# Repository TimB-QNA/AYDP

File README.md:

AYDP
====

The Autonomous Yacht Development Platform project. A project to develop a fully autonomous sailing yacht which can safely navigate between pre-defined waypoints.

Setting up AYDP:

You will need:
  A model yacht
  A Raspberry PI and SDCard
  A USB wifi dongle (which works in access point mode) - or a PI3
  An MPU-9150 IMU board
  An AYDP Interface board (see the hardware directory)
  And a variety of wires, power supplies etc. to put them all together.

First install a copy of Raspbian to the PI by downloading the latest image from http://www.raspberrypi.org/downloads there are loads of examples of how to burn the image to an SD Card, but you'll end up with a command something like:

dd bs=32K if=2014-01-07-wheezy-raspbian.img  of=/dev/sdb

Next, boot and log into the pi, then expand the partitions on the SD Card and enable the SSH server at bootup. Ensure that your PI has internet connection over a wired network link and install your wifi dongle (wired internet helps when you need to download packages). With the PI still connected to the internet, turn it into a wifi access point by following the instructions at http://elinux.org/RPI-Wireless-Hotspot except that there is no need to set up IPTables for NAT (unless you want to augment AYDP with network devices, in which case, you're probably smart enough to work out that you'll probably need NAT for any sensible debugging). The next major installation is I2C. This is disabled by default, but can by enabled by following the tutorial at https://learn.adafruit.com/adafruits-raspberry-pi-lesson-4-gpio-setup/configuring-i2c except for the bits about python (because this project is written in C++).

To get the i2c functionality to work, comment any lines in /etc/modprobe.d/raspi-blacklist.conf. and ensure the following modules are in /etc/modules:

snd-bcm2835
i2c-bcm2708
i2c-dev

At present, however, you'll only be able to run the code as root. Given that this is an utterly hideous idea (for a number of security reasons), we need to enable user access to the parts we need for the code to run. To avoid this, you need to add your user to the i2c group thus:

useradd -g i2c pi

Install sshfs for development work...
apt-get install sshfs
add "pi" user to the fuse group.

For development work you will need to install the following packages:

apt-get install qt4-dev-tools
apt-get install libusb-1.0-0-dev

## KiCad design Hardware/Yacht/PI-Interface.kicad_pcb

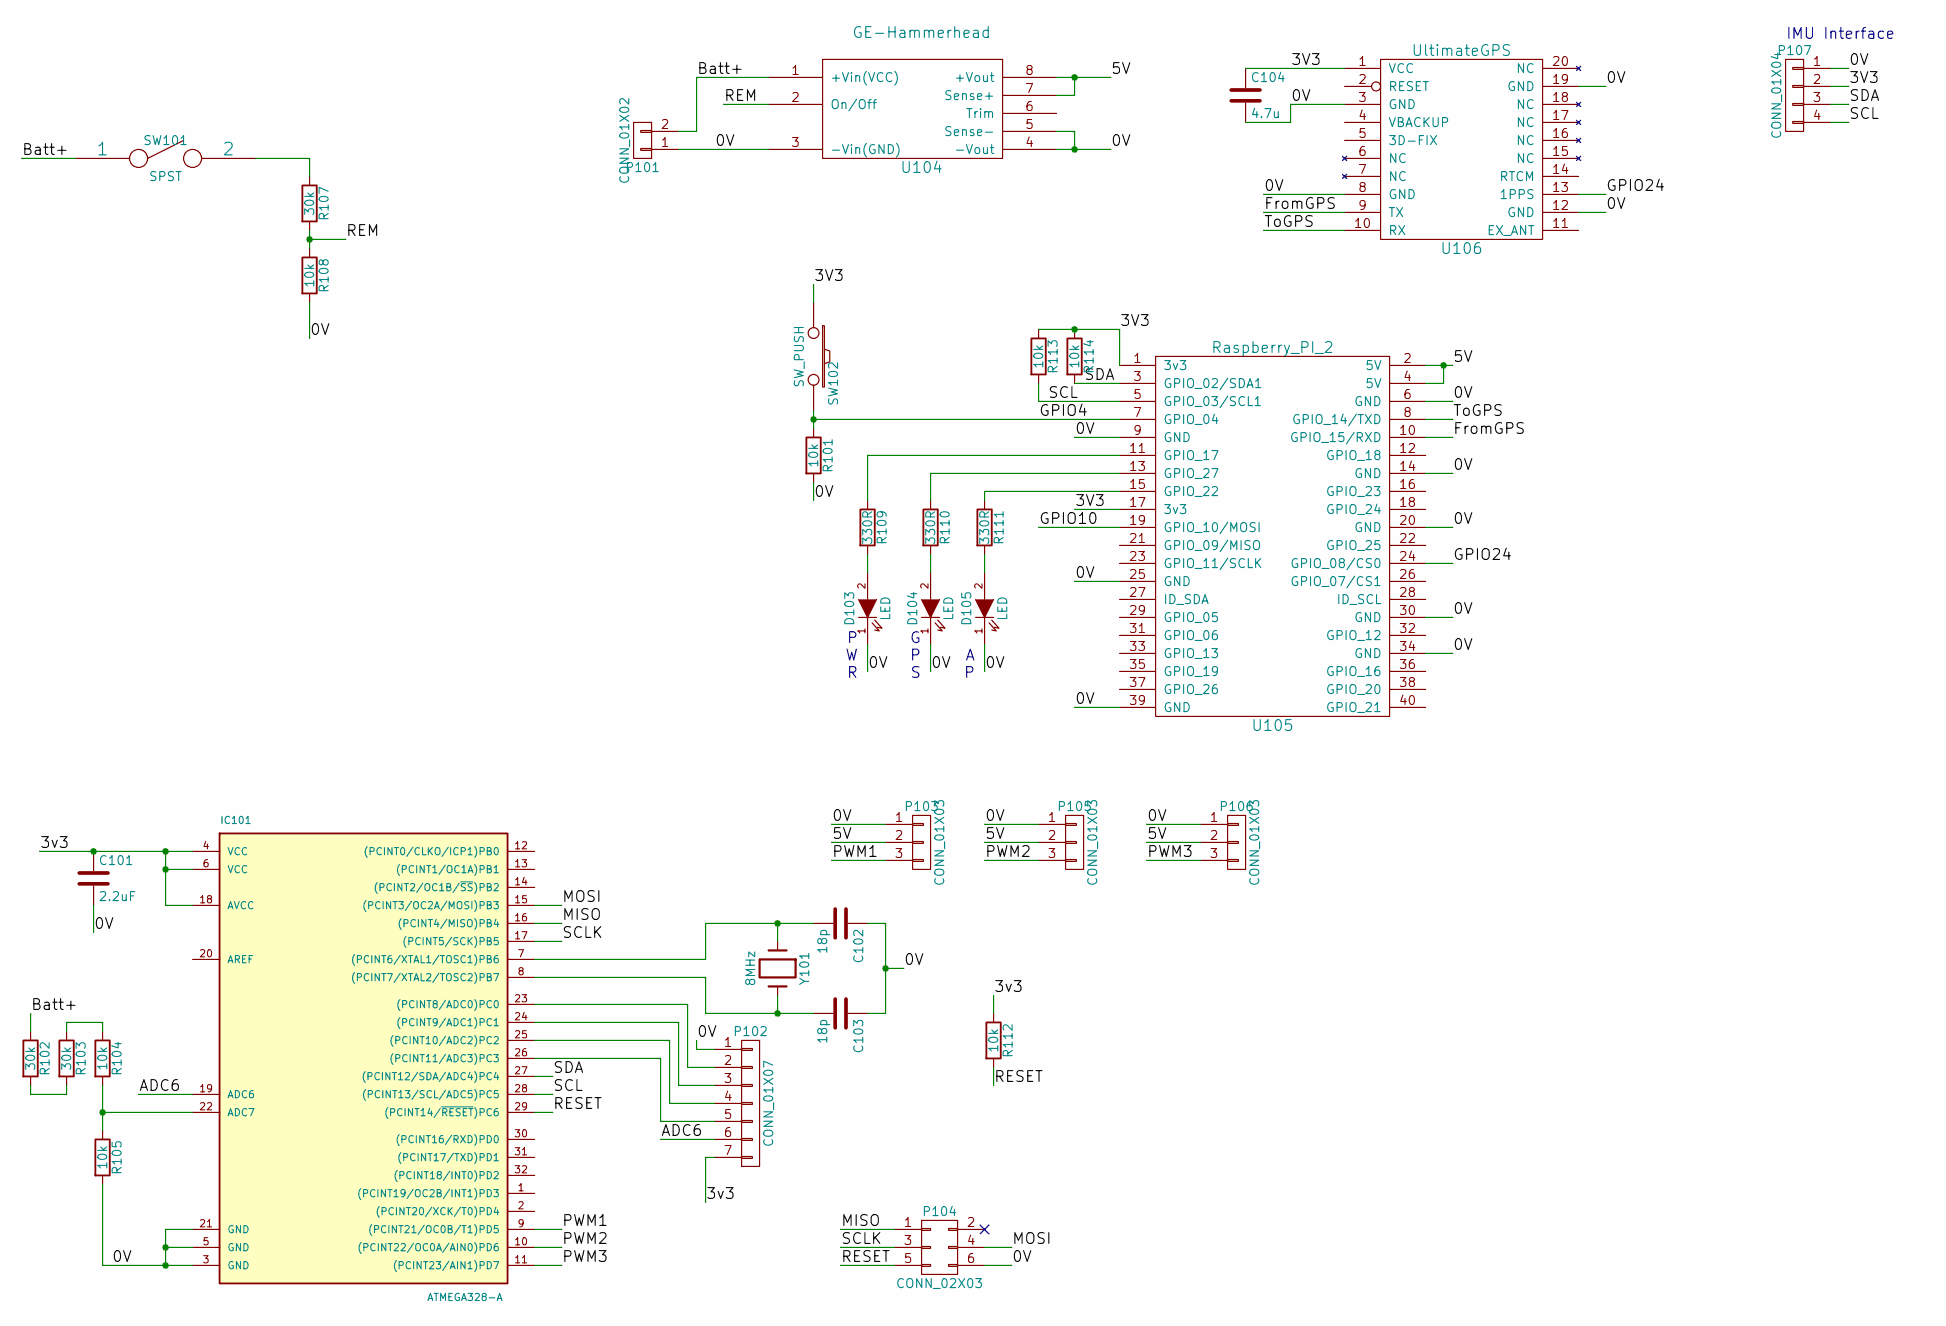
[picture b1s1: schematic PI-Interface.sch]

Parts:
C101: 2.2uF; C_0805
C102, C103: 18p; C_0805
C104: 4.7u; C_0805
D103, D104, D105: LED; LED-0805
IC101: ATMEGA328-A; TQFP-32_7x7mm_Pitch0.8mm
P101: CONN_01X02; BatteryConn10AWG
P102: CONN_01X07; Pin_Header_Straight_1x07
P103, P105, P106: CONN_01X03; Pin_Header_Straight_1x03
P104: CONN_02X03; Pin_Header_Straight_2x03
P107: CONN_01X04; Pin_Header_Straight_1x04
R101, R104, R105, R108, R112, R113, R114: 10k; R_0805
R102, R103, R107: 30k; R_0805
R109, R110, R111: 330R; R_0805
SW101: SPST; Pin_Header_Straight_1x02
SW102: SW_PUSH; Pin_Header_Straight_1x02
U104: GE-Hammerhead
U105: Raspberry_PI_2; R-PI2
U106: UltimateGPS
Y101: 8MHz; Crystal_HC49-SD_SMD

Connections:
/0V: C101.2, C102.1, C103.1, C104.2, D103.1 (K), D104.1 (K), D105.1 (K), IC101.3 (GND), IC101.5 (GND), IC101.21 (GND), P101.1, P102.1, P103.1, P104.6, P105.1, P106.1, P107.1, R101.2, R105.2, R108.2, U104.3 (-Vin(GND)), U104.4 (-Vout), U104.5 (Sense-), U105.6 (GND), U105.9 (GND), U105.14 (GND), U105.20 (GND), U105.25 (GND), U105.30 (GND), U105.34 (GND), U105.39 (GND), U106.3 (GND), U106.8 (GND), U106.12 (GND), U106.19 (GND)
/3V3: C101.1, C104.1, IC101.4 (VCC), IC101.6 (VCC), IC101.18 (AVCC), P102.7, P107.2, R112.1, R113.1, R114.1, SW102.1, U105.1 (3v3), U105.17 (3v3), U106.1 (VCC)
/5V: P103.2, P105.2, P106.2, U104.7 (Sense+), U104.8 (+Vout), U105.2 (5V), U105.4 (5V)
/ADC6: IC101.19 (ADC6), P102.6
/Batt+: P101.2, R102.1, SW101.1, U104.1 (+Vin(VCC))
/FromGPS: U105.10 (GPIO_15/RXD), U106.9 (TX)
/GPIO4: R101.1, SW102.2, U105.7 (GPIO_04)
/GPIO24: U105.24 (GPIO_08/CS0), U106.13 (1PPS)
/MISO: IC101.16 ((PCINT4/MISO)PB4), P104.1
/MOSI: IC101.15 ((PCINT3/OC2A/MOSI)PB3), P104.4
/PWM1: IC101.9 ((PCINT21/OC0B/T1)PD5), P103.3
/PWM2: IC101.10 ((PCINT22/OC0A/AIN0)PD6), P105.3
/PWM3: IC101.11 ((PCINT23/AIN1)PD7), P106.3
/REM: R107.2, R108.1, U104.2 (On/Off)
/RESET: IC101.29 ((PCINT14/~RESET~)PC6), P104.5, R112.2
/SCL: IC101.28 ((PCINT13/SCL/ADC5)PC5), P107.4, R113.2, U105.5 (GPIO_03/SCL1)
/SCLK: IC101.17 ((PCINT5/SCK)PB5), P104.3
/SDA: IC101.27 ((PCINT12/SDA/ADC4)PC4), P107.3, R114.2, U105.3 (GPIO_02/SDA1)
/ToGPS: U105.8 (GPIO_14/TXD), U106.10 (RX)
unnamed: C102.2, IC101.7 ((PCINT6/XTAL1/TOSC1)PB6), Y101.1
unnamed: C103.2, IC101.8 ((PCINT7/XTAL2/TOSC2)PB7), Y101.2
unnamed: D103.2 (A), R109.2
unnamed: D104.2 (A), R110.2
unnamed: D105.2 (A), R111.2
unnamed: IC101.22 (ADC7), R104.2, R105.1
unnamed: IC101.23 ((PCINT8/ADC0)PC0), P102.2
unnamed: IC101.24 ((PCINT9/ADC1)PC1), P102.3
unnamed: IC101.25 ((PCINT10/ADC2)PC2), P102.4
unnamed: IC101.26 ((PCINT11/ADC3)PC3), P102.5
unnamed: R102.2, R103.2
unnamed: R103.1, R104.1
unnamed: R107.1, SW101.2
unnamed: R109.1, U105.11 (GPIO_17)
unnamed: R110.1, U105.13 (GPIO_27)
unnamed: R111.1, U105.15 (GPIO_22)

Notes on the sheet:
IMU Interface
P W R
G P S
A P

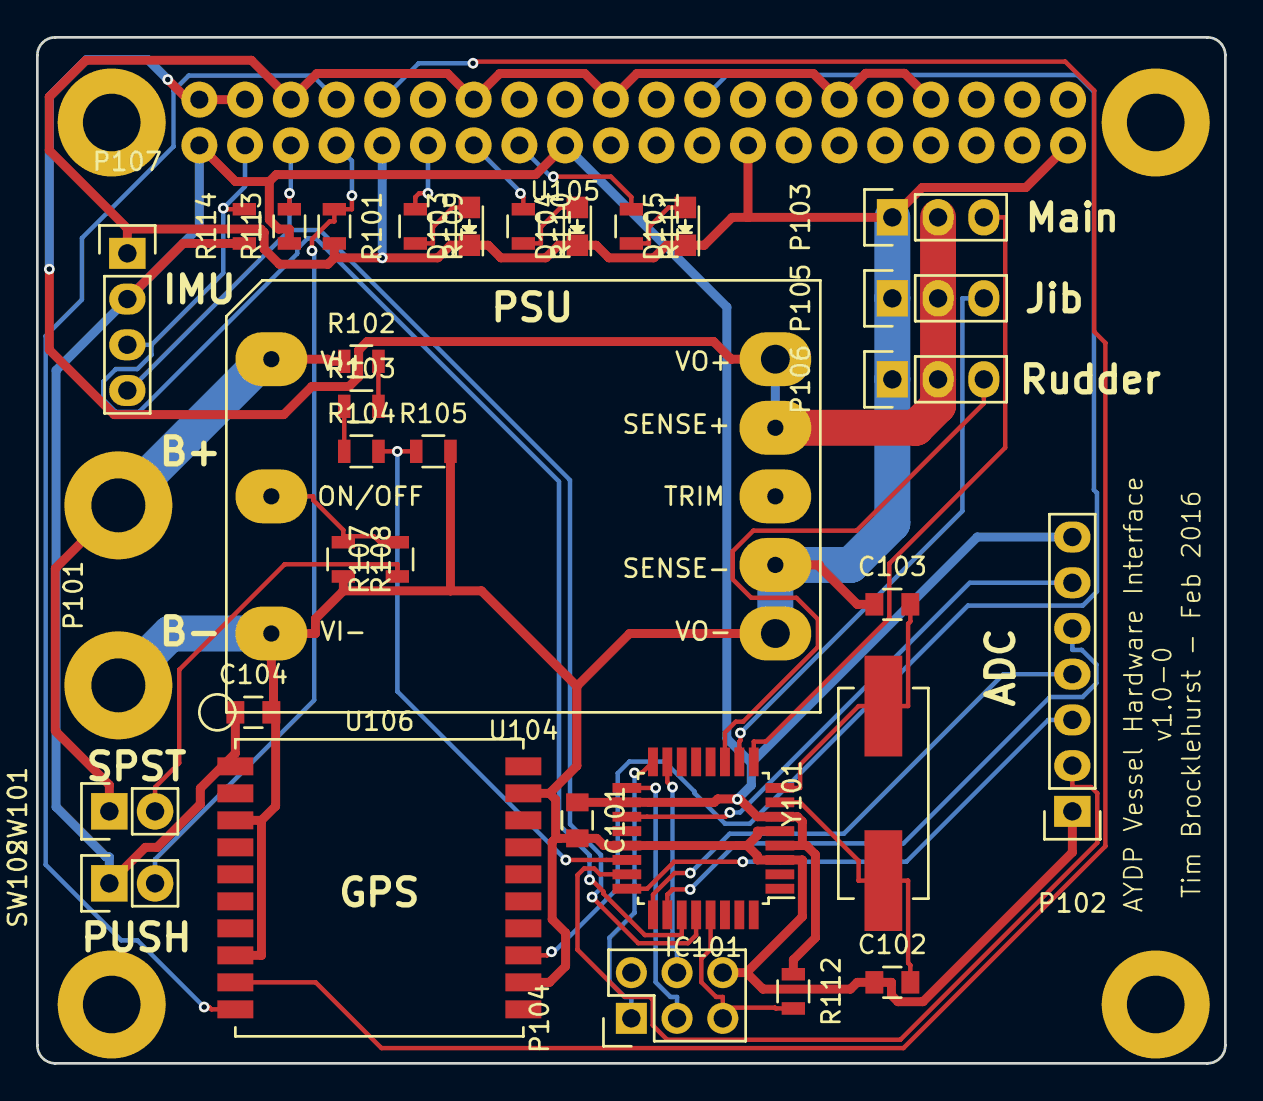
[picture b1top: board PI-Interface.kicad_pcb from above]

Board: 2 copper layers, 66.0 x 57.0 mm, 34 parts (0 on the bottom side), 35 nets.

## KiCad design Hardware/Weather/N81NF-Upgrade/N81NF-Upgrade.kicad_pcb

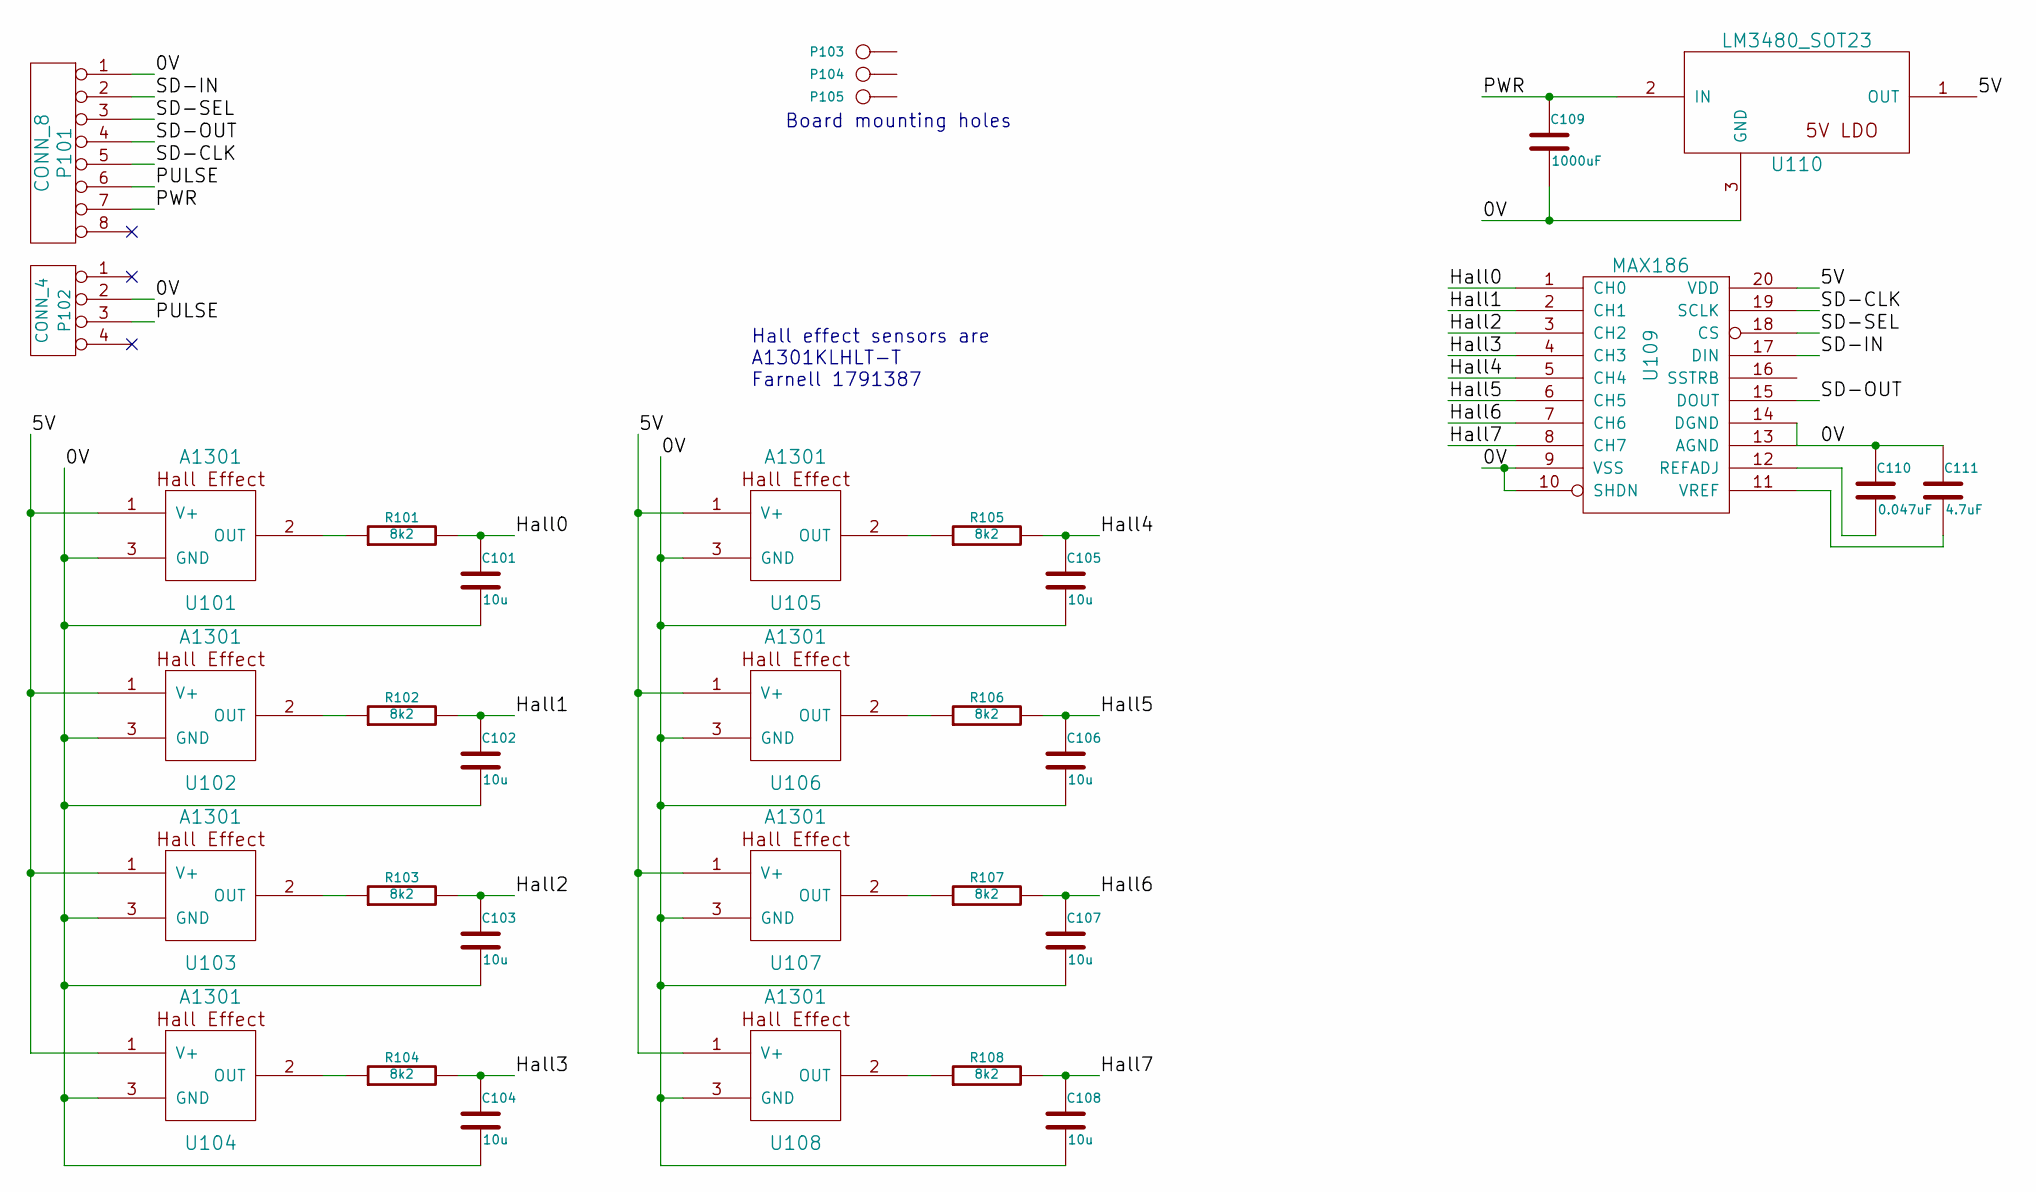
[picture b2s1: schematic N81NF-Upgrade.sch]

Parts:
C101, C102, C103, C104, C105, C106, C107, C108: 10u
C109: 1000uF
C110: 0.047uF
C111: 4.7uF
P101: CONN_8
P102: CONN_4
P103, P104, P105: CONN_1
R101, R102, R103, R104, R105, R106, R107, R108: 8k2
U101, U102, U103, U104, U105, U106, U107, U108: A1301
U109: MAX186
U110: LM3480_SOT23

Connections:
/0V: C101.2, C102.2, C103.2, C104.2, C105.2, C106.2, C107.2, C108.2, C109.2, C110.1, C111.1, P101.1, P102.2, U101.3 (GND), U102.3 (GND), U103.3 (GND), U104.3 (GND), U105.3 (GND), U106.3 (GND), U107.3 (GND), U108.3 (GND), U109.9 (VSS), U109.10 (SHDN), U109.13 (AGND), U109.14 (DGND), U110.3 (GND)
/5V: U101.1 (V+), U102.1 (V+), U103.1 (V+), U104.1 (V+), U105.1 (V+), U106.1 (V+), U107.1 (V+), U108.1 (V+), U109.20 (VDD), U110.1 (OUT)
/Hall0: C101.1, R101.2, U109.1 (CH0)
/Hall1: C102.1, R102.2, U109.2 (CH1)
/Hall2: C103.1, R103.2, U109.3 (CH2)
/Hall3: C104.1, R104.2, U109.4 (CH3)
/Hall4: C105.1, R105.2, U109.5 (CH4)
/Hall5: C106.1, R106.2, U109.6 (CH5)
/Hall6: C107.1, R107.2, U109.7 (CH6)
/Hall7: C108.1, R108.2, U109.8 (CH7)
/PULSE: P101.6, P102.3
/PWR: C109.1, P101.7, U110.2 (IN)
/SD-CLK: P101.5, U109.19 (SCLK)
/SD-IN: P101.2, U109.17 (DIN)
/SD-OUT: P101.4, U109.15 (DOUT)
/SD-SEL: P101.3, U109.18 (CS)
unnamed: R104.1, U104.2 (OUT)
unnamed: R106.1, U106.2 (OUT)
unnamed: R105.1, U105.2 (OUT)
unnamed: R107.1, U107.2 (OUT)
unnamed: R102.1, U102.2 (OUT)
unnamed: R101.1, U101.2 (OUT)
unnamed: R103.1, U103.2 (OUT)
unnamed: C110.2, U109.12 (REFADJ)
unnamed: C111.2, U109.11 (VREF)
unnamed: R108.1, U108.2 (OUT)

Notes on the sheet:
Board mounting holes
Hall effect sensors are A1301KLHLT-T Farnell 1791387

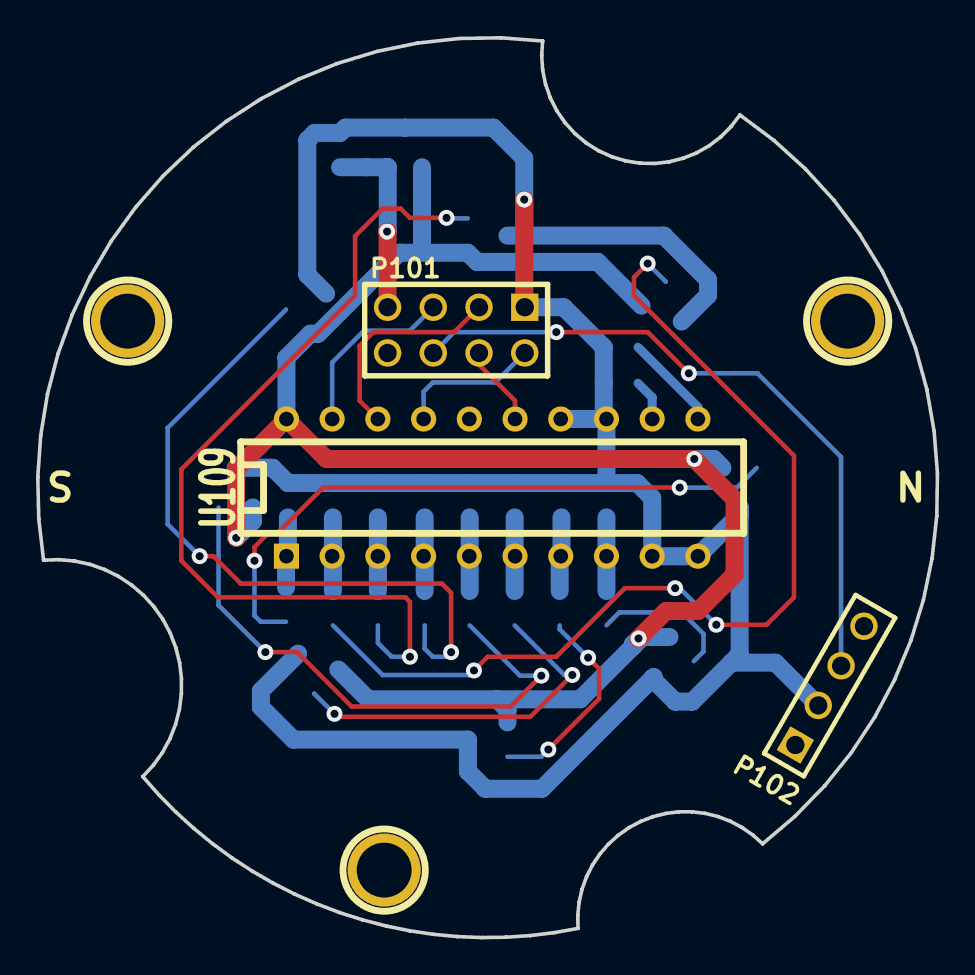
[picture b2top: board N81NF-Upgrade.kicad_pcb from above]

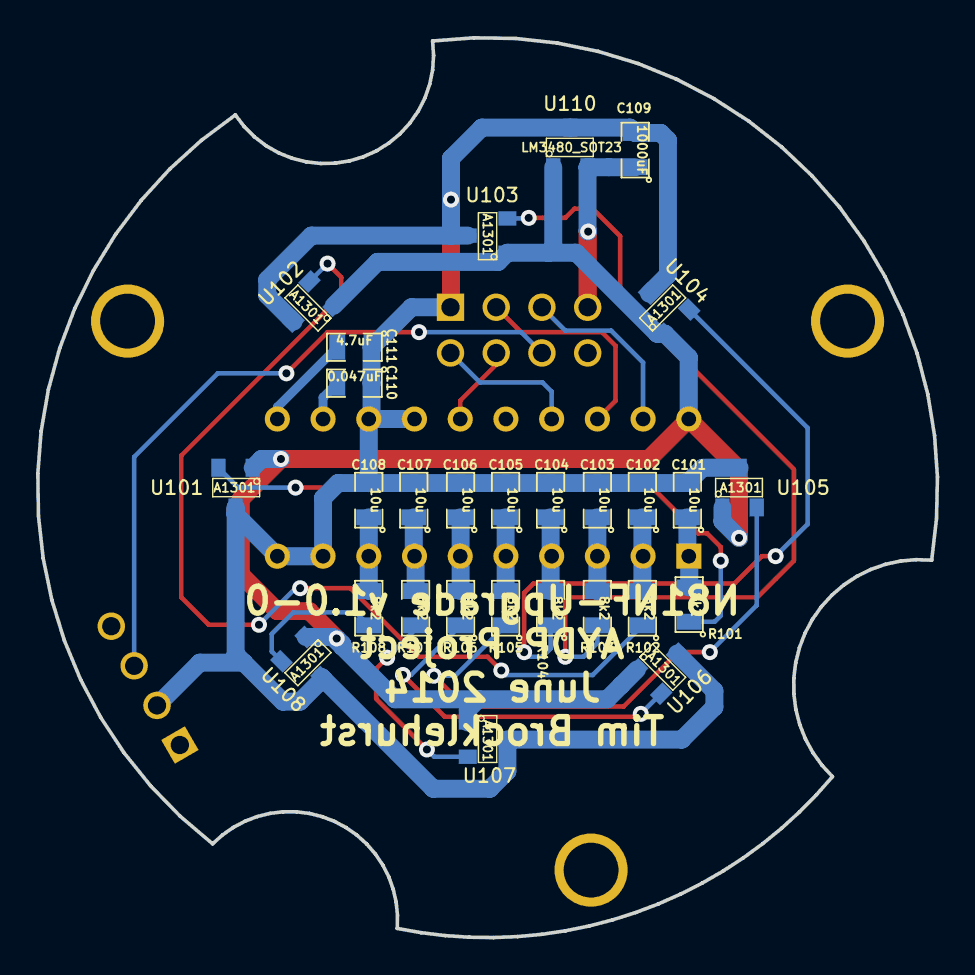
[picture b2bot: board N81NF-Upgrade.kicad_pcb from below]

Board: 2 copper layers, 50.0 x 50.0 mm, 34 parts (28 on the bottom side), 26 nets.

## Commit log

2014-06-21 Added notes after initial testing of some kit
2014-06-23 Added PCB design for the N81NF wind direction sensor.
2014-07-19 Basic wind indicator capability
2014-10-29 Using RTIMULib from Richards-Tech a submodule
2014-10-29 Bulk of code now broadly working. Comms link and sail control remaining.
2014-10-29 Library routines. These will probably disappear as they get merged into specific code bases
2014-10-29 Rough notes of the AYDP comms protocol (now out of date but I'll get it in a document eventually).
2014-10-29 Compressed IMU Drift results
2014-11-03 Mods to data store and comms link to support serialisation prior to sending
2015-01-03 Vessel AP updated to run on laptop
2015-01-03 Initial plugin for Aerotelemetry system
2015-01-03 Added example simulation using PID loop
2015-01-03 Example simulation code included
2015-01-25 Started to write documentation
2015-03-19 Current Hardware Documentation
2015-03-19 Removed backup file
2015-03-19 Software changes, including addition of speed and acceleration parameters to servo controller
2015-03-19 Comms link update and documentation
2015-04-11 Updates to comms protocol
2015-05-20 Protocol definitions expanded
2015-09-17 Example of controlling an aircraft in flightgear with the AYDP control system
2015-09-23 Corrections to comms protocol and improvements in robustness
2016-01-29 Added detail about system control message
2016-12-22 Major cleanup of directory structure
